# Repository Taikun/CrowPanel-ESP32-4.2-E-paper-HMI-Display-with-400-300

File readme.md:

### 1, Product picture

### 2, Product version number

|      | Hardware | Software | Remark |
| ---- | -------- | -------- | ------ |
| 1    | V1.0     | V1.0     | latest |

### 3, product information

- # Display Module Specifications

  - **Size**: 4.2 inch

  - **MCU**: ESP32-S3-WROOM-1-N8R8, up to 240 MHz

  - **Flash**: 8 MB

  - **PSRAM**: 8 MB

  - **Material**: Active Matrix Electrophoretic Display (AM EPD)

  - **Driver Chip**: SSD1683

  - **Resolution**: 400(H)*300(V) Pixel

  - **Pixel Pitch**: 0.212*0.212

  - **Viewing Angle**: Full Viewing Angle

  - **Communication Interface**: 3-/4-wire SPI

  - **Interface**:
    - UART0 x1
    - BAT x1
    - GPIO x1
    - TF Card Slot x1

  - **Button**:
    - Rotary Switch x1,
    - Menu Button x1, 
    - EXIT Button x1, 
    - REST Button x1, 
    - BOOT Button x1

  - **Development Environment**: Arduino IDE、ESP IDF、MicroPython

  - **Display Color**: Black and white

  - **Refresh Mode**: Partial refresh (saves more power)

  - **Display Operation Voltage**: 2.2~3.7V

  - **Operation Temperature**: -0~50℃

  - **Storage Temperature**: -25~70℃

  - **Active Area**: 84.8(H)\*63.6(L) (H*L)

### 4, Use the driver module

| Name    | dependency library     |
| ------- | ---------------------- |
| SSD1683 | EPD<br />version=1.0.0 |

### 5,Quick Start

##### Arduino IDE starts

1.Download the library files used by this product to the 'libraries' folder.

C:\Users\Documents\Arduino\libraries\

2.Open the Arduino IDE

3.Open the code configuration environment and burn it

### 6,Folder structure.

|--3D file： Contains 3D model files (.stp) for the hardware. These files can be used for visualization, enclosure design, or integration into CAD software.

|--Datasheet: Includes datasheets for components used in the project, providing detailed specifications, electrical characteristics, and pin configurations.

|--Eagle_SCH&PCB: Contains **Eagle CAD** schematic (`.sch`) and PCB layout (`.brd`) files. These are used for circuit design and PCB manufacturing.

|--example: Provides example code and projects to demonstrate how to use the hardware and libraries. These examples help users get started quickly. It now includes demos for OpenWeatherMap and TrueNAS.

|--factory_firmware: Stores pre-compiled factory firmware that can be directly flashed onto the device. This ensures the device runs the default functionality.

|--factory_sourcecode: Contains the source code for the factory firmware, allowing users to modify and rebuild the firmware as needed.

### 7,Pin definition

#define SCK 12

#define MOSI 11

#define RES 47

#define DC 46

#define CS 45

#define BUSY 48

## Create Images

[Image2cpp](https://javl.github.io/image2cpp/)

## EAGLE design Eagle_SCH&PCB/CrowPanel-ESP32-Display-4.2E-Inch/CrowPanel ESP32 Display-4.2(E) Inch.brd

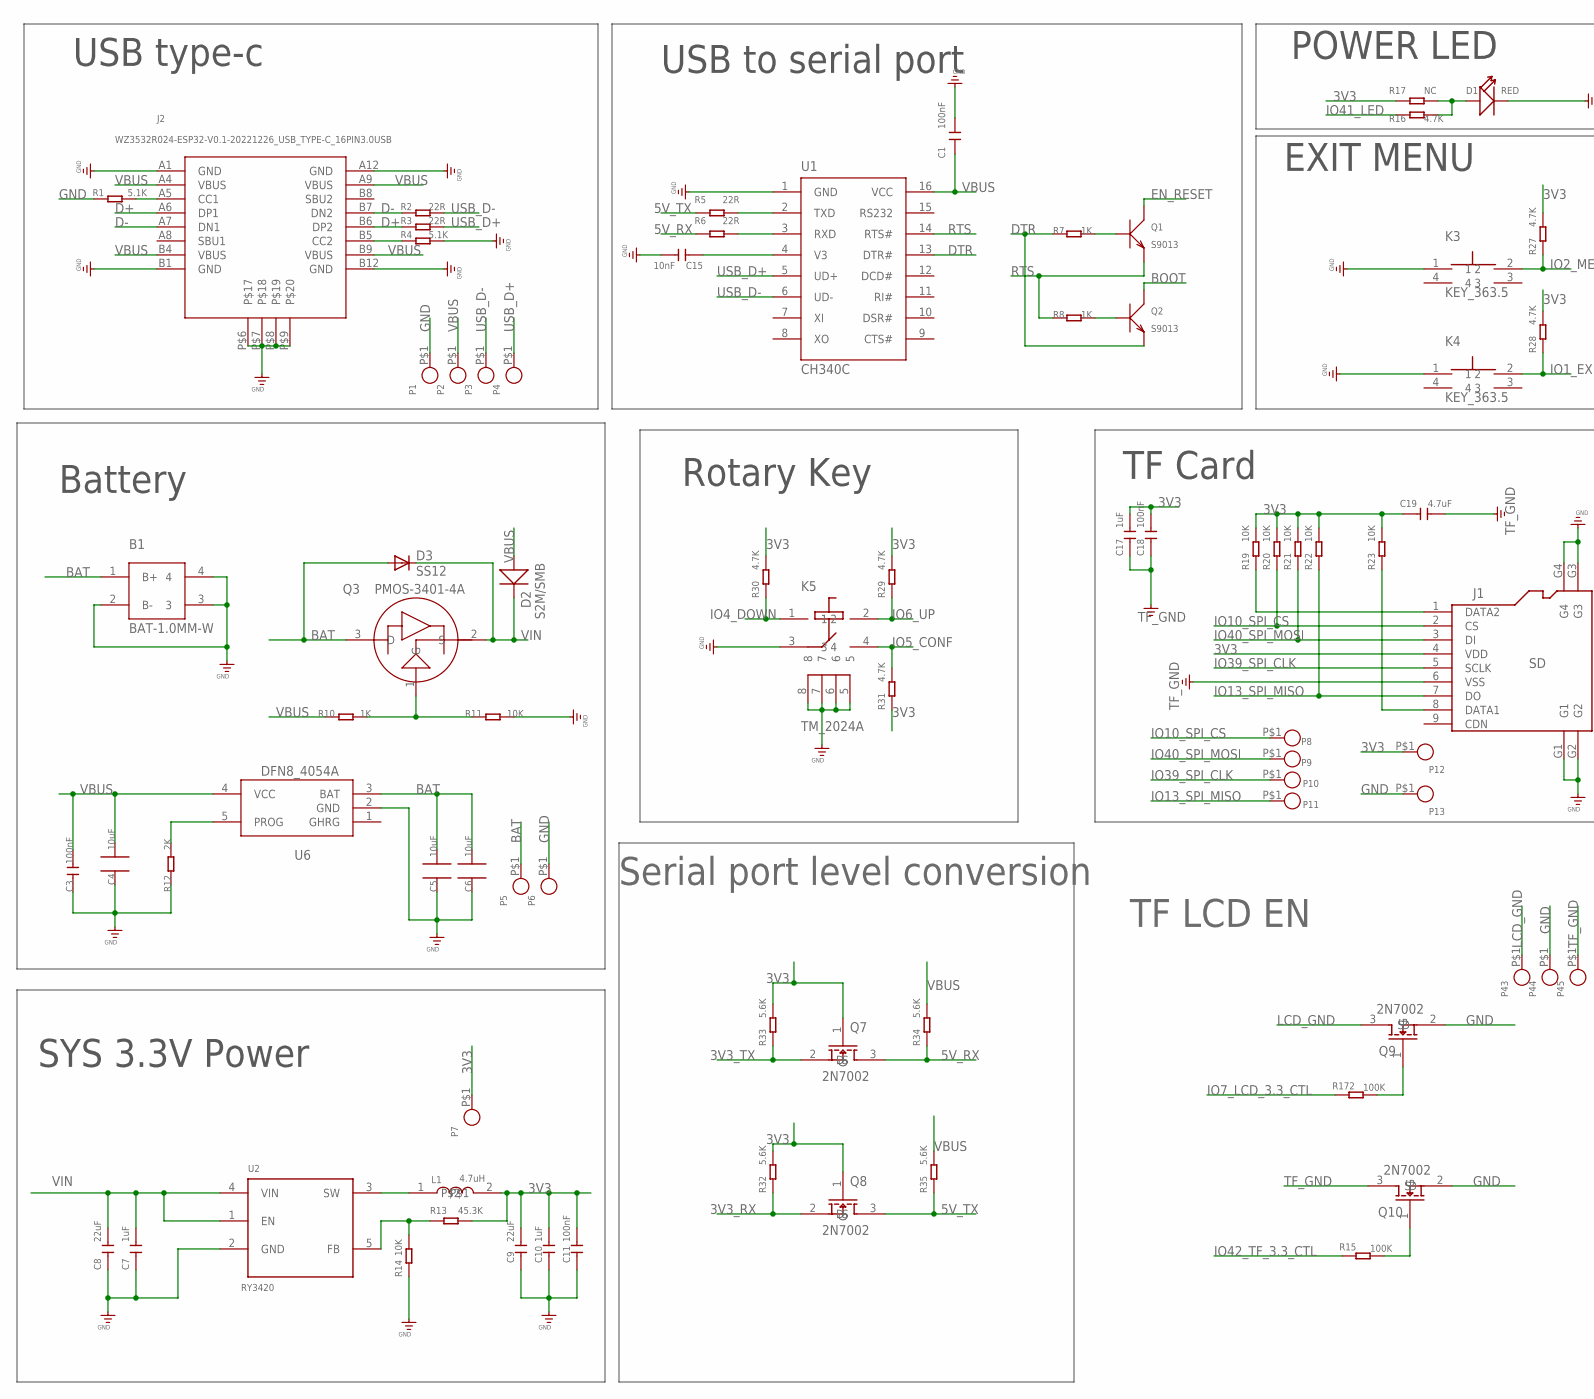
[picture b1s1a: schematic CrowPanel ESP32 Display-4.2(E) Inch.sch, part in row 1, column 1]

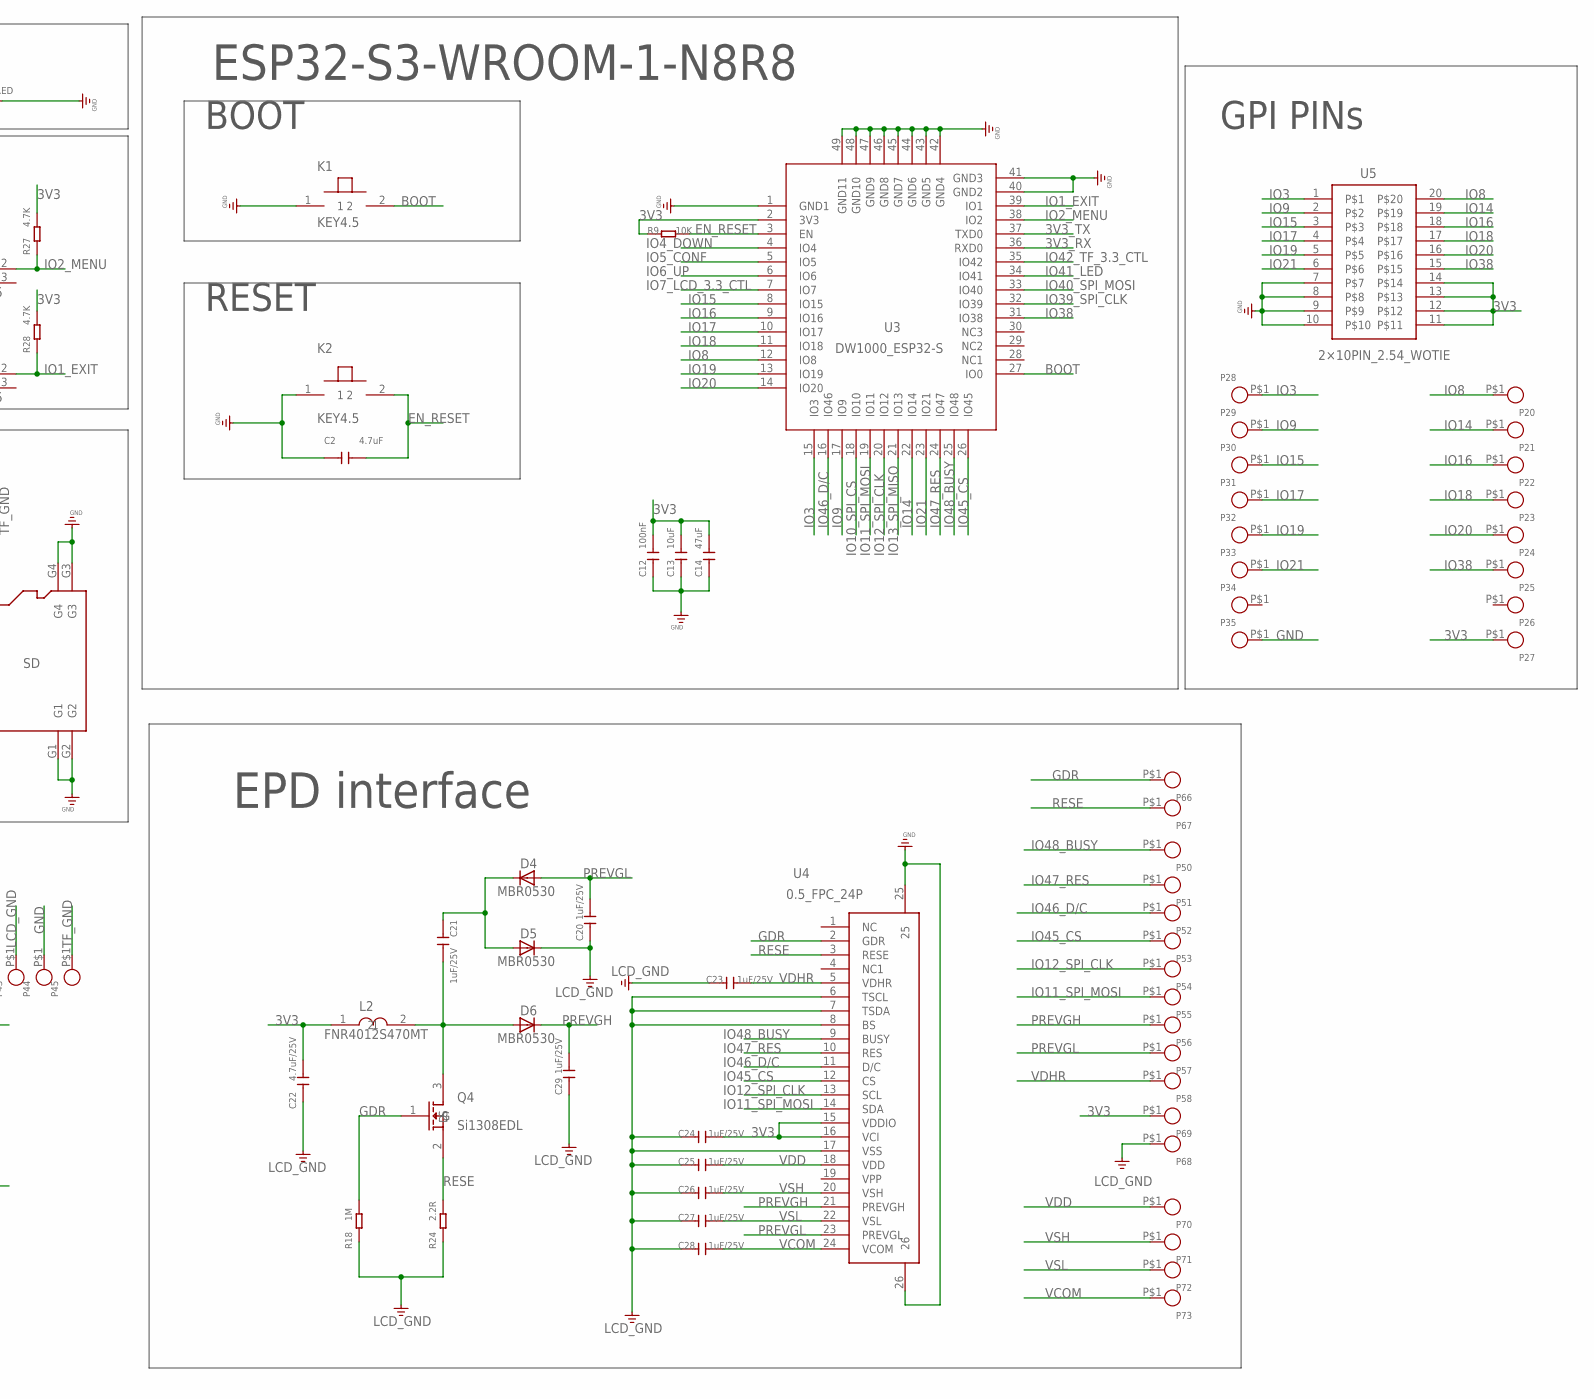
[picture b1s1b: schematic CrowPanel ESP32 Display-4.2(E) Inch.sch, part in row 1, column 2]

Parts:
B1: BAT-1.0MM-W; SH1.0MM-W
C1: 100nF; 0603
C2: 4.7uF; A_XBJ_0603
C3, C12, C18: 100nF; A9G_DISCRETE_C0603
C4, C5, C6: 10uF; CPT_SMD_0805_S
C7, C10: 1uF; A_XBJ_0603
C8, C9: 22uF; A_XBJ_0805
C11: 100nF; A_XBJ_0603
C13: 10uF; A9G_DISCRETE_C0603
C14: 47uF; A9G_DISCRETE_C0805
C15: 10nF; A_XBJ_0603
C17: 1uF; A9G_DISCRETE_C0603
C19: 4.7uF; A9G_DISCRETE_C0603
C20, C21, C23, C24, C25, C26, C27, C28, C29: 1uF/25V; A9G_DISCRETE_C0603
C22: 4.7uF/25V; A9G_DISCRETE_C0603
D1: RED; A_XBJ_DISCRETE_LED-0603
D2: S2M/SMB; DO-214AB_214AB
D3: SS12; DIODE_DO-214AC
D4, D5, D6: MBR0530; DIODE_SOD123
J1: SD; CONNECTOR_9P-SMD-W/-RING
J2: WZ3532R024-ESP32-V0.1-20221226_USB_TYPE-C_16PIN3.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; WZ3532R024-ESP32-V0.1-20221226_KEVIN_3.0TYPEC-SMD
K1, K2: KEY4.5; KEY-4.5
K3, K4: KEY_363.5; KEY_3*6*3.5
K5: TM_2024A
L1: 4.7uH; WZ2432R028-ESP32-V1.2-20231108_CD54_CD54
L2: FNR4012S470MT
P1, P2, P3, P4, P5, P6, P7, P8, P9, P10, P11, P12, P13, P20, P21, P22, P23, P24, P25, P26, P27, P28, P29, P30, P31, P32, P33, P34, P35, P43, P44, P45, P50, P51, P52, P53, P54, P55, P56, P57, P58, P66, P67, P68, P69, P70, P71, P72, P73: CROWPI_POW_PADPAD-1.0MM; CROWPI_POW_PAD-1.0MM
Q1, Q2: S9013; DISCRETE_SOT23$1
Q3: PMOS-3401-4A; DFN8_SOT-23
Q4: Si1308EDL; SOT-323_W
Q7, Q8, Q9, Q10: 2N7002; SOT23-3_W
R1, R4: 5.1K; R0603
R2, R3, R5, R6: 22R; R0603
R7, R8, R10: 1K; A9G_DISCRETE_R0603
R9, R11, R14, R19, R20, R21, R22, R23: 10K; A9G_DISCRETE_R0603
R12: 2K; A9G_DISCRETE_R0603
R13: 45.3K; A9G_DISCRETE_R0603
R15, R172: 100K; R0603
R16, R27, R28, R29, R30, R31: 4.7K; A9G_DISCRETE_R0603
R17: NC; A9G_DISCRETE_R0603
R18: 1M; A9G_DISCRETE_R0603
R24: 2.2R; A9G_DISCRETE_R0603
R32, R33, R34, R35: 5.6K; DISCRETE_R0603
U1: CH340C; A_XBJ_SOP-16
U2: RY3420; CROWBOT_-V1.0-20220525_A_XBJ_SOT23-5
U3: DW1000_ESP32-S; DW1000_ESP32-S3
U4: 0.5_FPC_24P
U5: 2×10PIN_2.54_WOTIE; 2*10PIN_2.54_WOTIE
U6: DFN8_4054A; DFN8_SOP23-5

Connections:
3V3: C9.2, C10.2, C11.2, C12.2, C13.2, C14.2, C17.2, C18.2, C19.2, C22.2, C24.1, J1.4 (VDD), L1.2, L2.1, P7.P$1, P12.P$1, P27.P$1, P69.P$1, Q7.1 (G), Q8.1 (G), R9.1, R13.2, R17.1, R19.2, R20.2, R21.2, R22.2, R23.2, R27.2, R28.2, R29.2, R30.2, R31.1, R32.2, R33.2, U3.2 (3V3), U4.15 (VDDIO), U4.16 (VCI), U5.11, U5.12, U5.13, U5.14
3V3_RX: Q8.2 (S), R32.1, U3.36 (RXD0)
3V3_TX: Q7.2 (S), R33.1, U3.37 (TXD0)
5V_RX: Q7.3 (D), R6.1, R34.1
5V_TX: Q8.3 (D), R5.1, R35.1
BAT: B1.1 (B+), C5.2, C6.2, D3.A, P5.P$1, Q3.3 (D), U6.3 (BAT)
BOOT: K1.2, Q2.3 (C), U3.27 (IO0)
D+: J2.A6 (DP1), J2.B6 (DP2), R3.1
D-: J2.A7 (DN1), J2.B7 (DN2), R2.1
DTR: Q2.2 (E), R7.1, U1.13 (DTR#)
EN_RESET: C2.2, K2.2, Q1.3 (C), R9.2, U3.3 (EN)
GDR: P66.P$1, Q4.1 (G), R18.2, U4.2 (GDR)
GND: B1.2 (B-), B1.3, B1.4, C1.2, C2.1, C3.1, C4.1, C5.1, C6.1, C7.1, C8.1, C9.1, C10.1, C11.1, C12.1, C13.1, C14.1, C15.2, D1.-, J1.G1, J1.G2, J1.G3, J1.G4, J2.A1 (GND), J2.A12 (GND), J2.B1 (GND), J2.B12 (GND), J2.P$6, J2.P$7, J2.P$8, J2.P$9, K1.1, K2.1, K3.1, K4.1, K5.3, K5.5, K5.6, K5.7, K5.8, P1.P$1, P6.P$1, P13.P$1, P35.P$1, P44.P$1, Q9.2 (S), Q10.2 (S), R1.1, R4.2, R11.2, R12.1, R14.1, U1.1 (GND), U2.2 (GND), U3.1 (GND1), U3.40 (GND2), U3.41 (GND3), U3.42 (GND4), U3.43 (GND5), U3.44 (GND6), U3.45 (GND7), U3.46 (GND8), U3.47 (GND9), U3.48 (GND10), U3.49 (GND11), U4.25, U4.26, U5.7, U5.8, U5.9, U5.10, U6.2 (GND)
IO1_EXIT: K4.2, R28.1, U3.39 (IO1)
IO2_MENU: K3.2, R27.1, U3.38 (IO2)
IO3: P28.P$1, U3.15 (IO3), U5.1
IO4_DOWN: K5.1, R30.1, U3.4 (IO4)
IO5_CONF: K5.4, R31.2, U3.5 (IO5)
IO6_UP: K5.2, R29.1, U3.6 (IO6)
IO7_LCD_3.3_CTL: R172.1, U3.7 (IO7)
IO8: P20.P$1, U3.12 (IO8), U5.20
IO9: P29.P$1, U3.17 (IO9), U5.2
IO10_SPI_CS: J1.2 (CS), P8.P$1, R20.1, U3.18 (IO10)
IO11_SPI_MOSI: P55.P$1, U3.19 (IO11), U4.14 (SDA)
IO12_SPI_CLK: P54.P$1, U3.20 (IO12), U4.13 (SCL)
IO13_SPI_MISO: J1.7 (DO), P11.P$1, R22.1, U3.21 (IO13)
IO14: P21.P$1, U3.22 (IO14), U5.19
IO15: P30.P$1, U3.8 (IO15), U5.3
IO16: P22.P$1, U3.9 (IO16), U5.18
IO17: P31.P$1, U3.10 (IO17), U5.4
IO18: P23.P$1, U3.11 (IO18), U5.17
IO19: P32.P$1, U3.13 (IO19), U5.5
IO20: P24.P$1, U3.14 (IO20), U5.16
IO21: P33.P$1, U3.23 (IO21), U5.6
IO38: P25.P$1, U3.31 (IO38), U5.15
IO39_SPI_CLK: J1.5 (SCLK), P10.P$1, U3.32 (IO39)
IO40_SPI_MOSI: J1.3 (DI), P9.P$1, R21.1, U3.33 (IO40)
IO41_LED: R16.1, U3.34 (IO41)
IO42_TF_3.3_CTL: R15.1, U3.35 (IO42)
IO45_CS: P53.P$1, U3.26 (IO45), U4.12 (CS)
IO46_D/C: P52.P$1, U3.16 (IO46), U4.11 (D/C)
IO47_RES: P51.P$1, U3.24 (IO47), U4.10 (RES)
IO48_BUSY: P50.P$1, U3.25 (IO48), U4.9 (BUSY)
LCD_GND: C20.1, C22.1, C23.2, C24.2, C25.2, C26.2, C27.2, C28.2, C29.1, D5.C, P43.P$1, P68.P$1, Q9.3 (D), R18.1, R24.1, U4.6 (TSCL), U4.7 (TSDA), U4.8 (BS), U4.17 (VSS)
unnamed: Q1.1 (B), R7.2
unnamed: R5.2, U1.2 (TXD)
unnamed: R6.2, U1.3 (RXD)
unnamed: Q2.1 (B), R8.2
unnamed: J2.A5 (CC1), R1.2
unnamed: Q3.1 (G), R10.2, R11.1
unnamed: Q9.1 (G), R172.2
unnamed: Q10.1 (G), R15.2
unnamed: R13.1, R14.2, U2.5 (FB)
unnamed: J1.1 (DATA2), R19.1
unnamed: L1.1, U2.3 (SW)
unnamed: J2.B5 (CC2), R4.1
unnamed: C15.1, U1.4 (V3)
unnamed: R12.2, U6.5 (PROG)
unnamed: J1.8 (DATA1), R23.1
unnamed: D1.+, R16.2, R17.2
unnamed: C21.1, D4.C, D5.A
unnamed: C21.2, D6.A, L2.2, Q4.3 (D)
PREVGH: C29.2, D6.C, P56.P$1, U4.21 (PREVGH)
PREVGL: C20.2, D4.A, P57.P$1, U4.23 (PREVGL)
RESE: P67.P$1, Q4.2 (S), R24.2, U4.3 (RESE)
RTS: Q1.2 (E), R8.1, U1.14 (RTS#)
TF_GND: C17.1, C18.1, C19.1, J1.6 (VSS), P45.P$1, Q10.3 (D)
USB_D+: P4.P$1, R3.2, U1.5 (UD+)
USB_D-: P3.P$1, R2.2, U1.6 (UD-)
VBUS: C1.1, C3.2, C4.2, D2.1 (+), J2.A4 (VBUS), J2.A9 (VBUS), J2.B4 (VBUS), J2.B9 (VBUS), P2.P$1, R10.1, R34.2, R35.2, U1.16 (VCC), U6.4 (VCC)
VCOM: C28.1, P73.P$1, U4.24 (VCOM)
VDD: C25.1, P70.P$1, U4.18 (VDD)
VDHR: C23.1, P58.P$1, U4.5 (VDHR)
VIN: C7.2, C8.2, D2.2 (-), D3.C, Q3.2 (S), U2.1 (EN), U2.4 (VIN)
VSH: C26.1, P71.P$1, U4.20 (VSH)
VSL: C27.1, P72.P$1, U4.22 (VSL)

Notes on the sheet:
USB type-c
USB to serial port
POWER LED
EXIT MENU
ESP32-S3-WROOM-1-N8R8
GPI PINs
EPD interface
TF Card
Rotary Key
SYS 3.3V Power
Battery
BOOT
RESET
Serial port level conversion
TF LCD EN

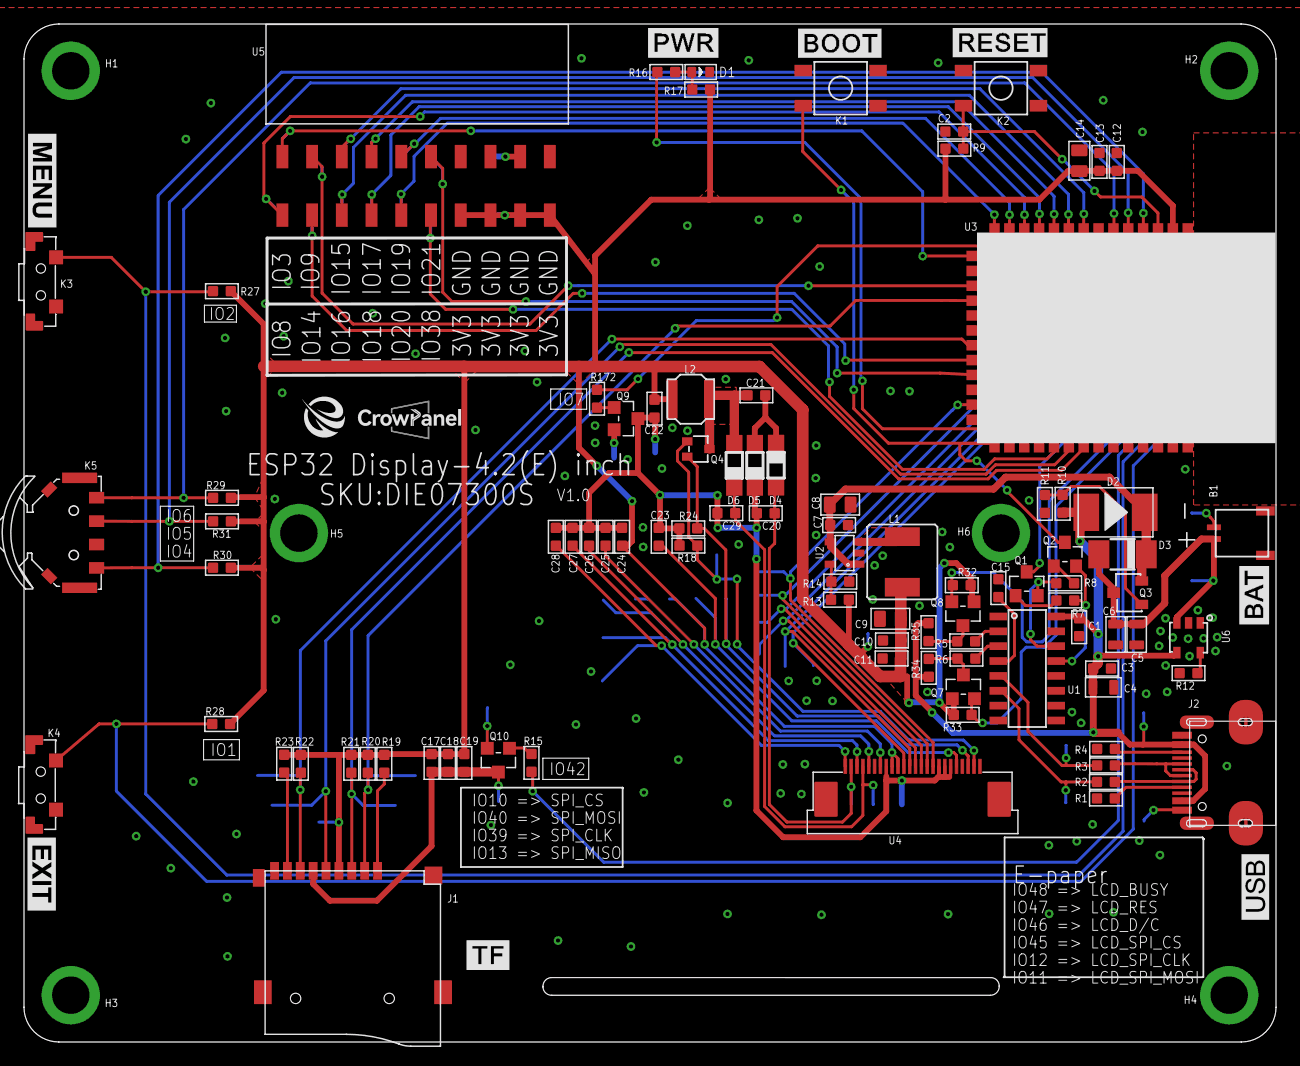
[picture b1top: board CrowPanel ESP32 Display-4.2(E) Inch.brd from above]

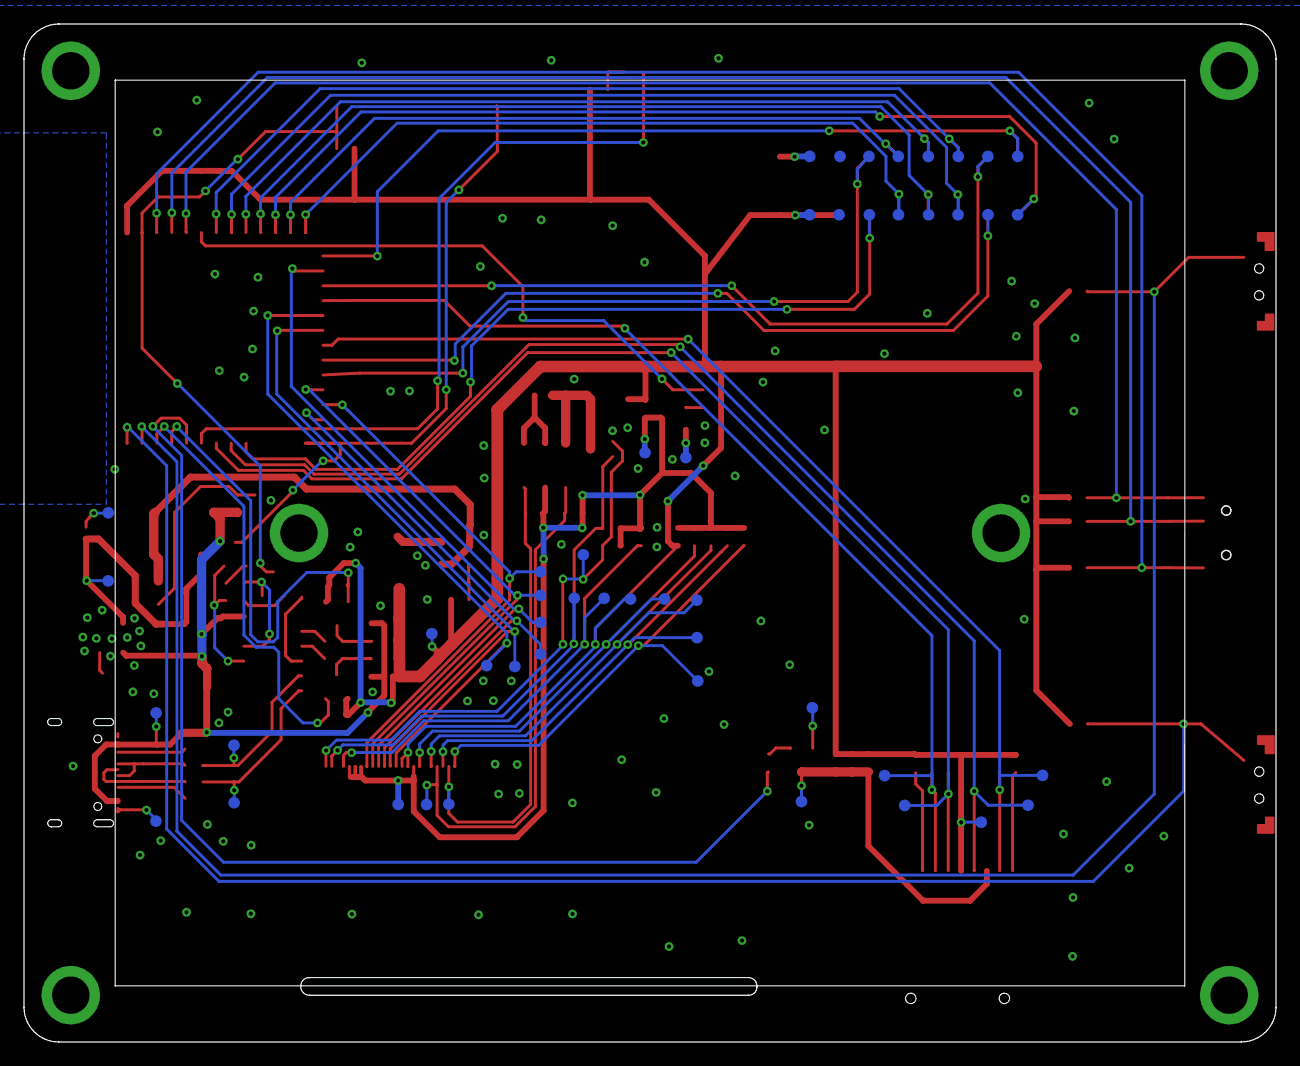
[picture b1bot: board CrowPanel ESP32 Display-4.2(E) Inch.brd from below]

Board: 2 copper layers, 107.0 x 87.0 mm, 143 parts (49 on the bottom side), 76 nets.

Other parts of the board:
U$30: LOGO-1
U$42: LOGO-MIN

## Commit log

2025-06-15 Improvements in security and interface
2025-06-15 Better interface
2025-06-18 Improvements in interface
2025-06-20 New sketch to monitor TrueNAS
2025-06-21 add .gitignore
2025-06-21 Progress Bars workign well
2025-06-22 Included new screens with Alarms and System Status
2025-06-22 Translate demos to English and update docs
2025-06-22 Added icon to active alarms
2025-06-22 Secrets help in english
2025-06-24 More time for each screen
